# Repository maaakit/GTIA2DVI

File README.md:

# GTIA2DVI

**GTIA2DVI** jest prototypem urządzenia umożliwiającego wyświetlanie obrazu cyfrowego w standardzie DVI przez
ośmiobitowe komputery Atari. Komputery te były produkowane w czasach gdy telewizja cyfrowa nie była publicznie dostępna 
przez co są zdolne generowac obraz jedynie w analogowych systemach PAL / NTSC. Większośc nowych telewizorów nie jest 
w stanie wyświetlić obrazu generowaniego przez Atari w zadowalającej jakosci.
Powstało wiele urządzeń oraz modów toru video Atari w mniejszym lub większym stopniu poprawiajacych jakość obrazu.
Jednak wszystkie te rozwiązania polegaja na zmianie parametrów obrazu analogowego a następnie jego digitalizację i 
konwersję do obrazu cyfrowego.

Ten projekt jest próbą rozwiązania problemu w pełni w domenie cyfrowej. Sercem projektu jest mikrokontroler RP2040 i biblioteka [PicoDVI](https://github.com/Wren6991/PicoDVI) dzięki której może on generować obraz DVI. GTIA2DVI w sposób software'owy ale z wykorzystaniem udostępnianego przez
RP2040 hardweru tj: DMA, PIO, Interpolator realizuje dekodowanie sygnałów generowanych przez Atari oraz tworzenie obrazu.

## Szczegóły techniczne

Obraz w komputerach Atari jest generowany przez układy specializowane ANTIC / GTIA. 
Ten drugi układ jest odpowiedzialny z generowanie sygnałów które są następnie przetwarzane przez układy analogowe
w obraz w systemie PAL/NTSC. Z dostępnych w internecie materiałów można wywnioskować że wszystkie sygnały wyjściowe GTIA
składające się na obraz wideo na pinach tego układu są cyfrowe. Są to następujące:

| nazwa sygnału | pin GTIA    | opis                                                                          |
|---------------|-------------|-------------------------------------------------------------------------------|
| OSC           | 28          | sygnał zegarowy synchronizujący pixele w trybie hires                         |
| CSYNC         | 25          | sygnał synchronizacji pionowej i poziomej                                     |
| LUM0 - LUM3   | 31,22,23,24 | 4-bitowy równoległa linia prezentująca wartość jasności pixela                |
| PAL           | 16          | sygnał zegara odpowiadającego za kodowanie koloru w systemie PAL              |
| COLOR         | 21          | wartość koloru okreeślona przez przesunięcie fazowe tego sygnału względem PAL |

Celem projektu jest generowanie obrazu cyfrowego na podstawie wyżej wymienionych sygnałów.

## Budowanie projektu

Należy mieć skonfigurowane środowisko SDK dla RP2040 (patrz https://datasheets.raspberrypi.com/pico/getting-started-with-pico.pdf)

Projekt mozna zbudwać posługując się IDE (np. Visual Studio Code)

lub z linii komend:

```shell

cd software
mkdir build
cd build
cmake -DCMAKE_BUILD_TYPE=Release ..
make

```

Wynikiem procesu budowania jest plik: `build/gtia2dvi/gtia2dvi.uf2` który nalezy wgrać do RP2040.

Uwaga! Jedynie plik zbudowane w `BUILD_TYPE=Release` zapewniają poprawne działanie programu

## Uruchomienie

Po zamontowaniu urządzenia w Atari sygnał DVI będzie dostępny automatycznie. W podstawowej konfiguracji generowany jest 
sygnał monochroamtyczny w odcieniach szarości. 
Dekodowanie sygnału **chroma** jest w fazie eksperymentalnej i może zostać włączone z poziomu menu po uprzednim skalibrowaniu.

Urządzenie posiada 3 przyciski:

* **RESET** służący do resetowania
* **BTN_A** słuzący do aktywacji menu podczas restartu oraz do wybierania opcji menu. Poza menu przełącza tryb wyświetlania mono / color
* **BTN_B** służacy do aktywacji wybranej opcj menu. Poza menu pełni funkcję stopklatki (zatrzymuje odświerzanie obrazu Atari)

Aby wejść do menu systemowego należy trzymac wciśnięty przycisk **BTN_A** w trakcie restartu urządzenia (za pomocą przycisku reset)

## Opcje menu

* Informacja o statusie kalibracji
* [Kalibracja sygnału chroma](#kalibracja-sygnału-chroma)
* [Procedura ustawiania potencjometru CADJ](#ustawienie-potencjometru-CADJ)
* Włączanie / wyłączanie dekodowania
* Przywrócenie do ustawień fabrycznych
* Wyjście z menu i powrót do normalnego trybu
* Zapisanie wprowadzonych zmian

## Kalibracja sygnału chroma

Należy uruchomić Atari Basic i załadować program CALSCR którego listing znajduje się w folderze `atari`
Program wyświetla obraz służący do kalibracji. 

Gdy jego tworzenie zostanie zakończone należy przejść do menu GTIA2DVI.
Następnie wybrać opcję `Chroma Calibration` i ją potwierdzić.

W czasie kalibracji prezentowany jest na żywo aktualny postęp budowania mapy kolorów.
Proces składa się zdwóch przebiegów i trwa ok. 95 sekund. Po tym czasie urządzenie zapisze zarejestrowane mapy kolorów 
w automatycznie pamięci FLASH i automatycznie się zrestartuje.

## Ustawienie potencjometru CADJ

W pewnych przypadkach aby uzyskać dobry rezultat kalibracji niezbędne jest dostrojenie potencjometru CADJ.
W trakcie tego procesu Atari powinno wyświetlać ten sam obraz jak w procesie kalibracji (CALSCR).
Należy znaleźć takie położenie w którym na obrazie nie występują żółte kropki oraz ilość szarych jest jak najmniejsza.
Po zakończeniu regulacji należy przycisnąć RESET na płytce GTIA2DVI

## Dodatkowe wskazówki

Najlepszą jakość wyświetlanego koloru można osiągnąc na płytach które zapewniają niski poziom szumów i zakłóceń sygnałów.
Dodatkowe rozszerzenia np. U1MB, SIDE2 generują zauważalne zakłócenia w wyświetlanym kolorze
Pozytywny wpływ na generowany obraz mogą mieć:
* Zamiana dławika L37 na rezystor 470ohm
* Wymiana kondensatora C50 na nowy o niskim ESR
* Wymina potencjometru CADJ (R38) na precyzyjny wieloobrotowy
* zastosowanie Static RAM (niezweryfikowane)

## Troubleshooting

1) **Obraz DVI nie jest wyświetlany** należy:
   * wyłączyć Atari i zdemontowac GTIA2DVI
   * zweryfikować wszystkie połączenia
   * wgrać jeden z przykładowych programów z repozytorium PicoDVI (https://github.com/Wren6991/PicoDVI)

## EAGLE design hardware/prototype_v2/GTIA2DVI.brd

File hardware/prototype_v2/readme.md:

# Lista elementów

| symbol   | nazwa                       | wartość |
|----------|-----------------------------|---------|
| C1 - C3  | kondensator                 | 100nF   |
| R1 - R8  | rezystor                    | 270R    |
| R9 - R14 | nie montować                |         |
| X1       | Raspberry Pi Pico           |         |
| IC2      | 74AC541                     |         |
| IC4P     | podstawka 40pin             |         |
| IC5P     | pin header 2x20             |         |
| DVI      | złącze DVI lub kompatybilne |         |
| SWITCH   | 3 mikrowłączniki do masy    |         |

## procedura pierwszego uruchomiania

1) Po zmontowaniu zweryfikować wszystkie połączenia
2) Nie montować GTIA i nie umieszczać modułu na płycie Atari
3) Podpiąć kablem usb do PC trzymając wciśnięty przycisk BOOTSEL
4) wgrać wsad gtia2dvi.uf2
5) podłączyć kablem do TV/monitora i uruchomić menu konfiguracyjne (trzymahąc wciśnięty BTN_A zresetowac moduł)
6) po prawidłowym zweryfikowaniu wyświetlanego obrazu odłączyć wszystkie połączenia
7) zamontować GTIA
8) podłączyć do płyty Atari
9) zweryfikować połączenia i uruchomić Atari

**Uwaga !**
To jest urządzenie DIY. Sam odpowiadasz za jego prawidłowe zmontowanie, uruchomienie i wszystkie szkody które może wyrządzić!

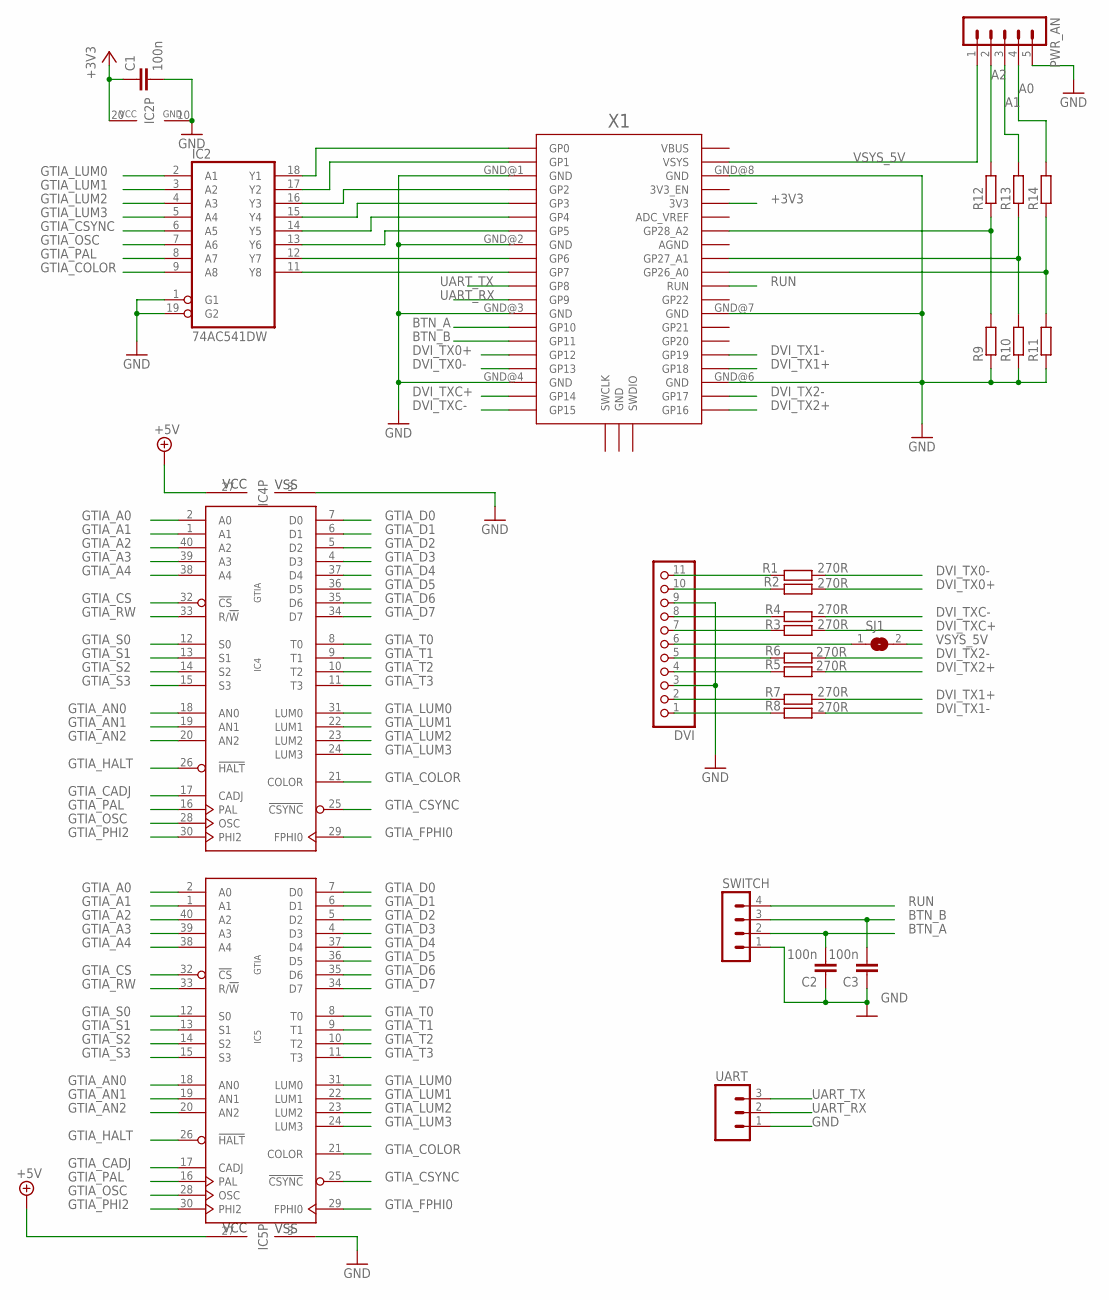
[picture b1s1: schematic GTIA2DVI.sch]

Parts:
C1, C2, C3: 100n; C0805
DVI: PINHD-1X11; 1X11
IC2: 74AC541DW; SO20W
IC4, IC5: GTIA; DIL40
PWR_AN: MA05-1
R1, R2, R3, R4, R5, R6, R7, R8: 270R; M0805
R9, R10, R11, R12, R13, R14: R-EU_M0805; M0805
SJ1: SJ
SWITCH: MA04-1
UART: MA03; 03P
X1: RPI_PICO_IG-TH; RPI_PICO_TH

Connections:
+3V3: C1.1, IC2.20 (VCC), X1.3V3
+5V: IC4.27 (VCC), IC5.27 (VCC)
A0: PWR_AN.4, R14.2
A1: PWR_AN.3, R13.2
A2: PWR_AN.2, R12.2
BTN_A: C2.2, SWITCH.2, X1.GP10
BTN_B: C3.2, SWITCH.3, X1.GP11
DVI_TX0+: R2.2, X1.GP12
DVI_TX0-: R1.2, X1.GP13
DVI_TX1+: R7.2, X1.GP18
DVI_TX1-: R8.2, X1.GP19
DVI_TX2+: R5.2, X1.GP16
DVI_TX2-: R6.2, X1.GP17
DVI_TXC+: R3.2, X1.GP14
DVI_TXC-: R4.2, X1.GP15
GND: C1.2, C2.1, C3.1, DVI.3, DVI.9, IC2.1 (G1), IC2.10 (GND), IC2.19 (G2), IC4.3 (VSS), IC5.3 (VSS), PWR_AN.5, R9.1, R10.1, R11.1, SWITCH.1, UART.1, X1.GND@1 (GND), X1.GND@2 (GND), X1.GND@3 (GND), X1.GND@4 (GND), X1.GND@6 (GND), X1.GND@7 (GND), X1.GND@8 (GND)
GP0: IC2.18 (Y1), X1.GP0
GP1: IC2.17 (Y2), X1.GP1
GP2: IC2.16 (Y3), X1.GP2
GP3: IC2.15 (Y4), X1.GP3
GP4: IC2.14 (Y5), X1.GP4
GP5: IC2.13 (Y6), X1.GP5
GP6: IC2.12 (Y7), X1.GP6
GP7: IC2.11 (Y8), X1.GP7
GTIA_A0: IC4.2 (A0), IC5.2 (A0)
GTIA_A1: IC4.1 (A1), IC5.1 (A1)
GTIA_A2: IC4.40 (A2), IC5.40 (A2)
GTIA_A3: IC4.39 (A3), IC5.39 (A3)
GTIA_A4: IC4.38 (A4), IC5.38 (A4)
GTIA_AN0: IC4.18 (AN0), IC5.18 (AN0)
GTIA_AN1: IC4.19 (AN1), IC5.19 (AN1)
GTIA_AN2: IC4.20 (AN2), IC5.20 (AN2)
GTIA_CADJ: IC4.17 (CADJ), IC5.17 (CADJ)
GTIA_COLOR: IC2.9 (A8), IC4.21 (COLOR), IC5.21 (COLOR)
GTIA_CS: IC4.32 (!CS), IC5.32 (!CS)
GTIA_CSYNC: IC2.6 (A5), IC4.25 (!CSYNC), IC5.25 (!CSYNC)
GTIA_D0: IC4.7 (D0), IC5.7 (D0)
GTIA_D1: IC4.6 (D1), IC5.6 (D1)
GTIA_D2: IC4.5 (D2), IC5.5 (D2)
GTIA_D3: IC4.4 (D3), IC5.4 (D3)
GTIA_D4: IC4.37 (D4), IC5.37 (D4)
GTIA_D5: IC4.36 (D5), IC5.36 (D5)
GTIA_D6: IC4.35 (D6), IC5.35 (D6)
GTIA_D7: IC4.34 (D7), IC5.34 (D7)
GTIA_FPHI0: IC4.29 (FPHI0), IC5.29 (FPHI0)
GTIA_HALT: IC4.26 (!HALT), IC5.26 (!HALT)
GTIA_LUM0: IC2.2 (A1), IC4.31 (LUM0), IC5.31 (LUM0)
GTIA_LUM1: IC2.3 (A2), IC4.22 (LUM1), IC5.22 (LUM1)
GTIA_LUM2: IC2.4 (A3), IC4.23 (LUM2), IC5.23 (LUM2)
GTIA_LUM3: IC2.5 (A4), IC4.24 (LUM3), IC5.24 (LUM3)
GTIA_OSC: IC2.7 (A6), IC4.28 (OSC), IC5.28 (OSC)
GTIA_PAL: IC2.8 (A7), IC4.16 (PAL), IC5.16 (PAL)
GTIA_PHI2: IC4.30 (PHI2), IC5.30 (PHI2)
GTIA_RW: IC4.33 (R/!W), IC5.33 (R/!W)
GTIA_S0: IC4.12 (S0), IC5.12 (S0)
GTIA_S1: IC4.13 (S1), IC5.13 (S1)
GTIA_S2: IC4.14 (S2), IC5.14 (S2)
GTIA_S3: IC4.15 (S3), IC5.15 (S3)
GTIA_T0: IC4.8 (T0), IC5.8 (T0)
GTIA_T1: IC4.9 (T1), IC5.9 (T1)
GTIA_T2: IC4.10 (T2), IC5.10 (T2)
GTIA_T3: IC4.11 (T3), IC5.11 (T3)
unnamed: DVI.11, R1.1
unnamed: DVI.10, R2.1
unnamed: DVI.8, R4.1
unnamed: DVI.7, R3.1
unnamed: DVI.5, R6.1
unnamed: DVI.4, R5.1
unnamed: DVI.2, R7.1
unnamed: DVI.1, R8.1
unnamed: R9.2, R12.1, X1.GP28_A2
unnamed: R10.2, R13.1, X1.GP27_A1
unnamed: R11.2, R14.1, X1.GP26_A0
RUN: SWITCH.4, X1.RUN
UART_RX: UART.2, X1.GP9
UART_TX: UART.3, X1.GP8
VSYS_5V: DVI.6, PWR_AN.1, SJ1.1, SJ1.2, X1.VSYS

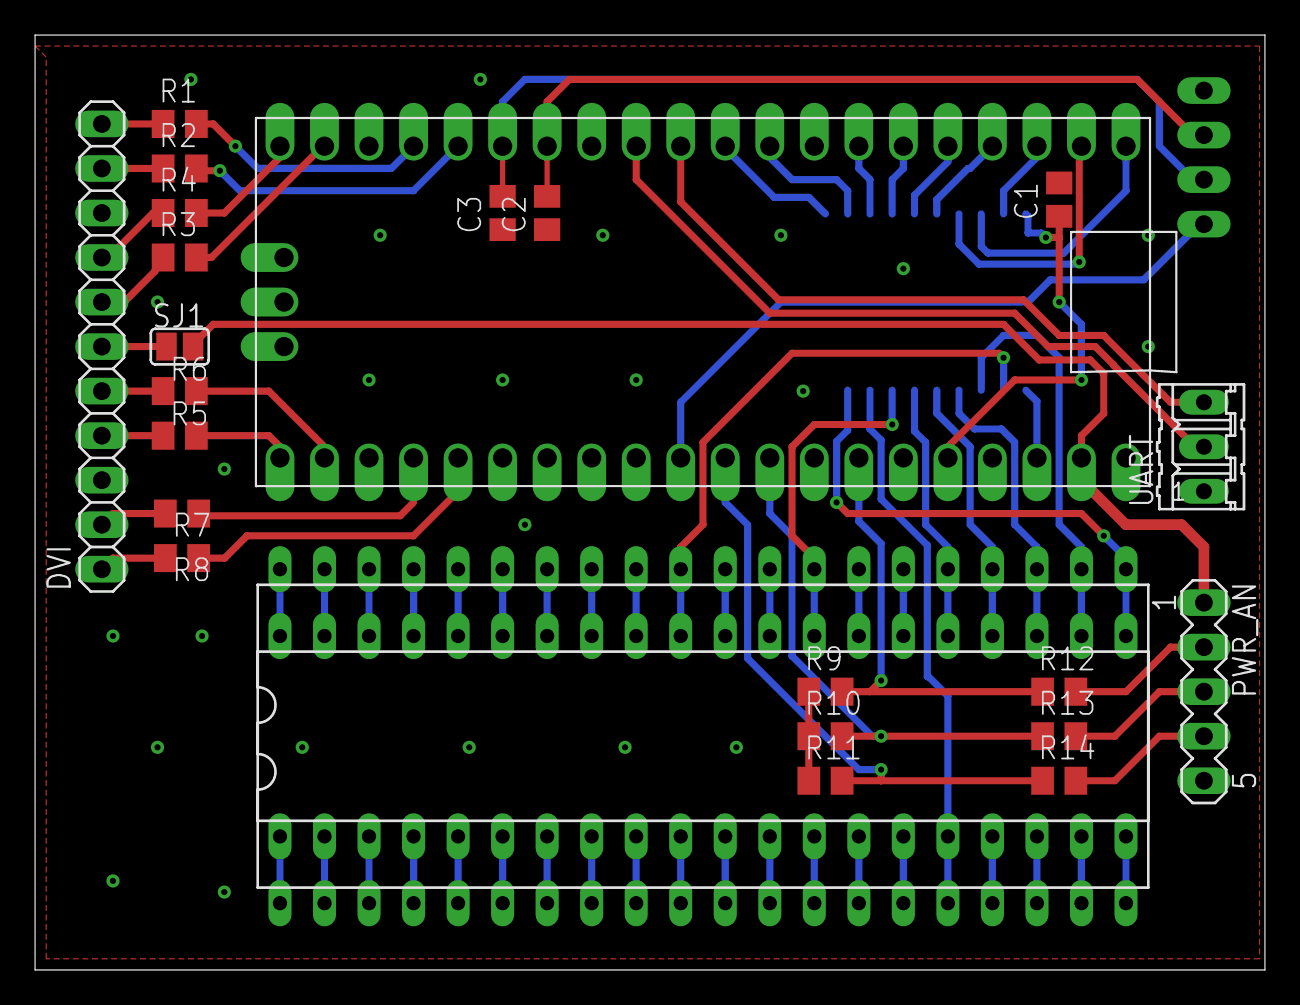
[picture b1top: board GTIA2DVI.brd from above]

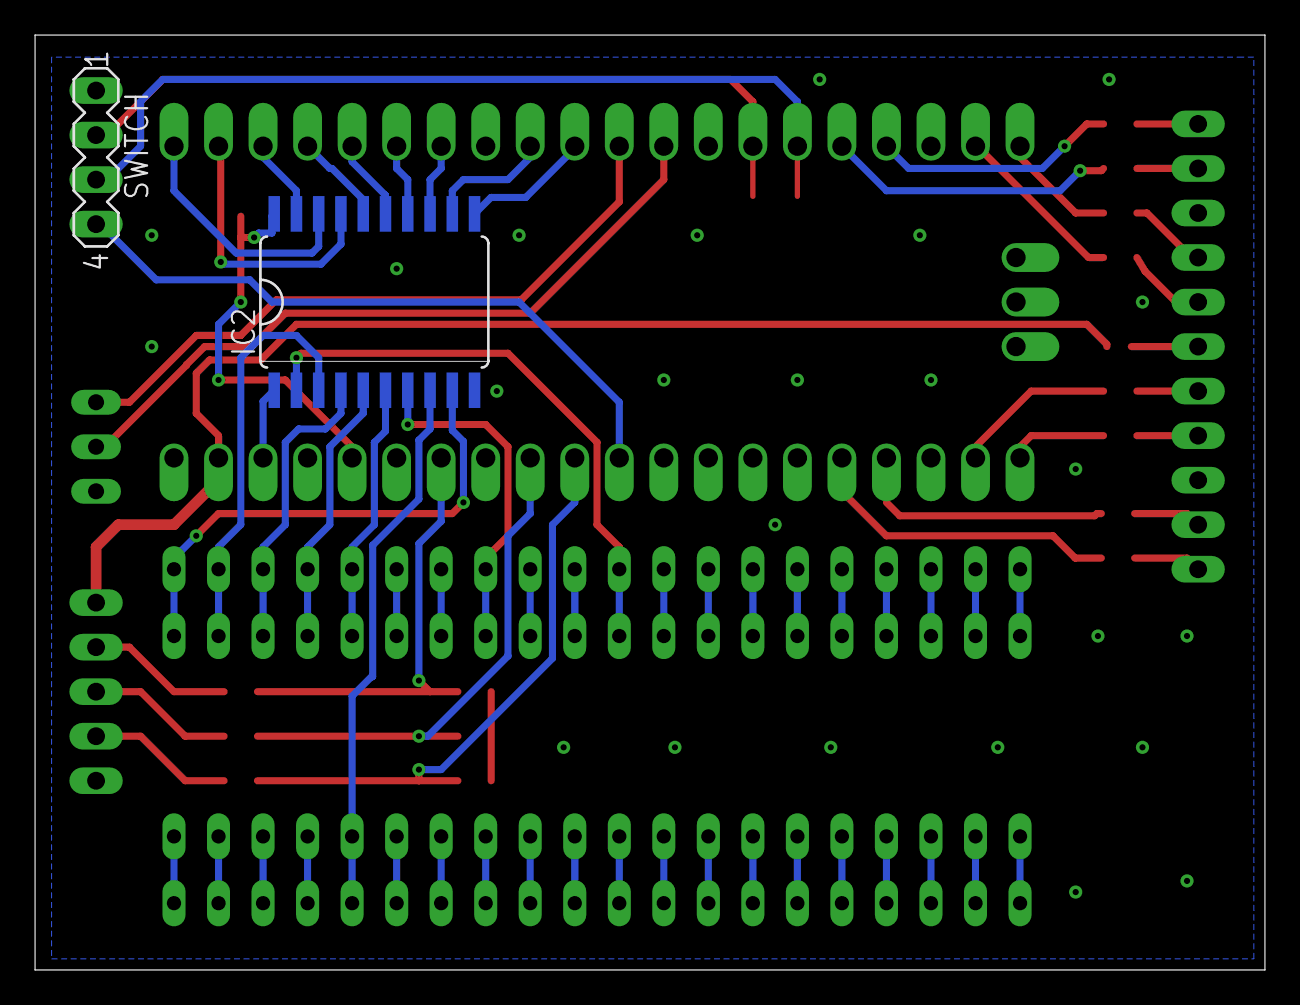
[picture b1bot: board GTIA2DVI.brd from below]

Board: 2 copper layers, 70.2 x 53.3 mm, 26 parts (2 on the bottom side), 77 nets.

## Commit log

2024-01-12 buttons and menu introduced
2024-01-15 [wip] luma calibration menu and others
2024-01-17 [wip] fixed all flash access problems
2024-01-18 small menu fix
2024-01-18 new resolution 768x576 50Hz
2024-01-18 screen parametrization; can switch chroma /luma only at runtime
2024-01-20 prompt before factory reset and chroma calibration
2024-01-21 cleaning code
2024-01-21 rainbow effect in "Drunk Chessboard" reduced
2024-01-23 more reliable and deterministic statisctcs driven calibration process
2024-01-23 chroma.h code cleanup
2024-01-24 uart_log introduced / code separated in folders
2024-01-25 uart logging added
2024-01-27 more logs / schematic added
2024-01-27 added atari basic listings for calibration program
2024-01-27 readme.md
2024-01-27 prototype hwd folder renamed
2024-02-11 uart output switched to gpio pin 21
2024-02-11 preparation for clock synchronization
2024-03-08 chroma calibration visualization critical code in scratch_y region separated color and pal pio programs
2024-03-26 bulk changes
2024-03-28 defined DUMP_FEATURE rename
2024-03-28 voltage decreased to 1.25
2024-03-28 more info on pixel dump
2024-03-28 freeze screen when BTN_B pressed
2024-04-02 tmp_optimized_color_decoding
2024-04-03 out of memory
2024-04-03 wrong_chroma
2024-04-03 fixed with interpolator optimization
2024-04-05 restored pixel dump feature
2024-04-05 some optimizations and more comments
2024-04-05 schematic updated: buttons pins changed uart added
2024-04-08 color burst condition data dump every 500 frames
2024-04-08 definition for not matched colors
2024-04-15 fixed delay for pal
2024-04-16 optimizations in color decoding
2024-04-22 chroma decoder v3
2024-04-29 optimizations
2024-04-29 moved to hardware UART buttons and UART pins changed
2024-04-29 core voltage decreased to 1.25V
2024-04-29 BTN_B freezes screen updates
2024-05-06 framebuffer chcanged from rgb565 to indexed 8b palette to save some RAM
2024-05-09 uart_log_flush moved to dvi core
2024-05-10 osc triggered chroma samples
2024-05-11 chroma calibration rewriten
2024-05-31 improved calibratoion - wip
2024-06-02 new feature for dumping single gtia data in csv format
2024-06-03 better quality and fine tuning
2024-06-04 added calibration saving rewritten chroma and luma video display
2024-06-06 fixed problem in second phase of calibration
2024-06-07 burst condition dump feature
2024-06-11 auto chroma shift adjustment feature added
2024-06-13 pot adjustment procedure / calibration optimizations
2024-06-19 multithreading syncing in uart logger
2024-06-19 chroma calibration improvements
2024-06-21 chroma processing improvements
2024-06-21 config is logged to uart on boot
2024-06-21 extended mode for calibration step2
2024-06-28 new calibration screen
2024-06-29 actual git commit info in uart log, menu screen and filename
2024-06-29 auto clean build dir
2024-06-29 cleaning build dir moved to begin
2024-06-29 removing build binaries instead of cleaning build/gtia2dvi completly
2024-06-30 removed git hash from binary build file names
2024-06-30 Revert "new calibration screen"
    This reverts commit 95aed511
2024-06-30 git line ending config
2024-07-01 submodule fix
2024-07-01 fixed bad file
2024-07-01 updated Atari calscr files
2024-07-02 docs updated
2024-07-07 encoding fixed
2024-07-20 chroma sample size extended to 32b
2024-07-20 dump color mapping to uart and bigger diagram
2024-07-28 fixed error when wrong color wasdraw during calibration
2024-07-31 PAL clock generation on pin 22
2024-08-18 [wip] v1
2024-08-18 [wip] v2
2024-09-04 burst condition logged to uart
2024-09-16 fixed buttons software debouncing problem

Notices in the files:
parts and their libraries:
eagle-6.5.0-atari: Copyright (c) 2010
Copyright (c) 2009
This library is licensed under the
Creative Commons Attribution 3.0 United States License.
